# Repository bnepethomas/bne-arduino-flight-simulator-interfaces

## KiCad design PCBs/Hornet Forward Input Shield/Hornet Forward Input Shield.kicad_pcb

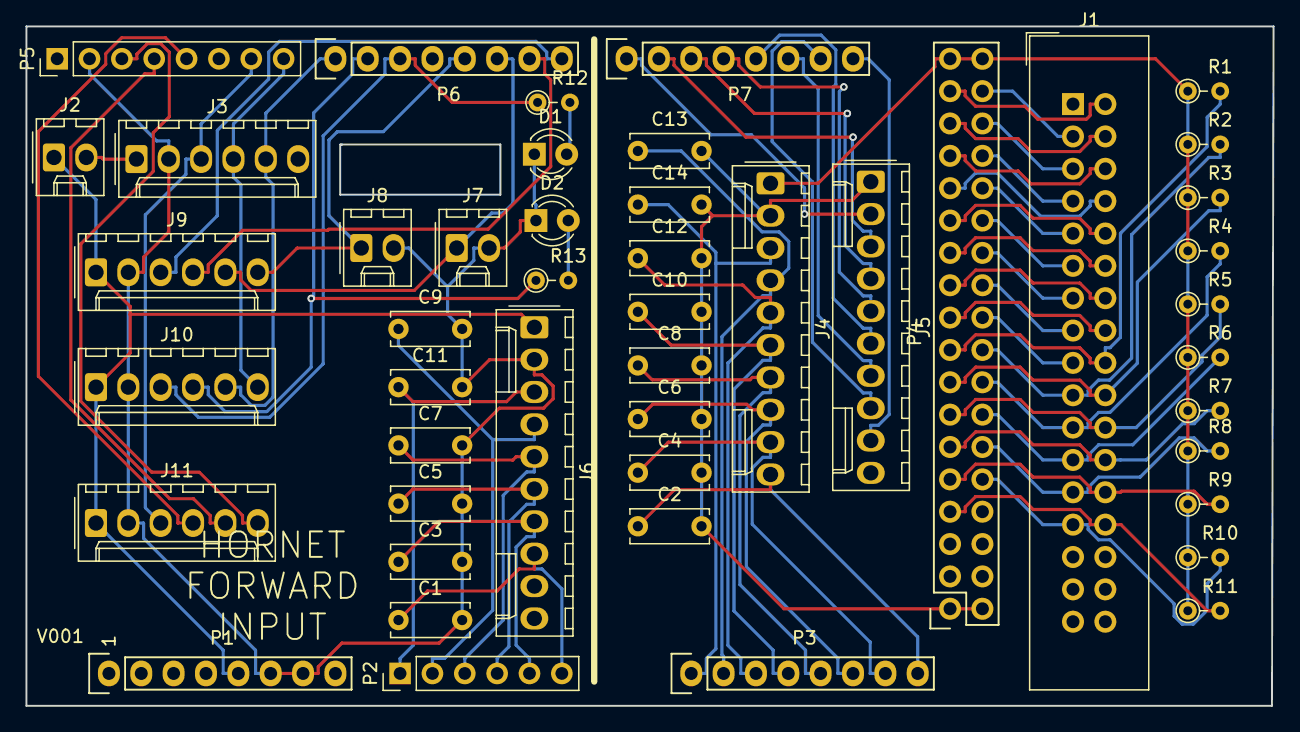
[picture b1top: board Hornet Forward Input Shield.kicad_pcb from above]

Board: 2 copper layers, 97.9 x 53.3 mm, 47 parts (0 on the bottom side), 68 nets.

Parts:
C1, C2, C3, C4, C5, C6, C7, C8, C9, C10, C11, C12, C13, C14: C; C_Disc_D6.0mm_W2.5mm_P5.00mm
D1: GREEN; LED_D3.0mm
D2: RED; LED_D3.0mm
J1: MATRIX INPUT; IDC-Header_2x17_P2.54mm_Vertical
J2: 5V to Max7219; Molex_1x02_P2.54mm_Vertical
J3: 7219 OUT; Molex_1x06_P2.54mm_Vertical
J4: ANALOG B; Molex_1x10_P2.54mm_Vertical
J5: ENCODERS; Molex_1x10_P2.54mm_Vertical
J6: ANALOG A; Molex_1x10_P2.54mm_Vertical
J7: Address Select 0; Molex_1x02_P2.54mm_Vertical
J8: Address Select 1; Molex_1x02_P2.54mm_Vertical
J9: DIGITAL A; Molex_1x06_P2.54mm_Vertical
J10: DIGITAL B; Molex_1x06_P2.54mm_Vertical
J11: DIGITAL C; Molex_1x06_P2.54mm_Vertical
P1: Power; Socket_Strip_Arduino_1x08
P2: Analog; PinHeader_1x06_P2.54mm_Vertical
P3: Analog; Socket_Strip_Arduino_1x08
P4: Digital; Socket_Strip_Arduino_2x18
P5: PWM; PinHeader_1x08_P2.54mm_Vertical
P6: PWM; Socket_Strip_Arduino_1x08
P7: Communication; Socket_Strip_Arduino_1x08
R1, R2, R3, R4, R5, R6, R7, R8, R9, R10, R11, R12, R13: R; PT_R_Axial_DIN0204_L3.6mm_D1.6mm_P2.54mm_Vertical

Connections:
+5V: J4.1, P4.35, P4.36, R1.1, R2.1, R3.1, R4.1, R5.1, R6.1, R7.1, R8.1, R9.1, R10.1, R11.1
+5VL: J2.1, J6.1, J9.1, J10.1, J11.1, P1.5
/14(Tx3): J5.2, P7.1
/15(Rx3): J5.3, P7.2
/16(Tx2): J5.4, P7.3
/17(Rx2): J5.5, P7.4
/18(Tx1): J5.6, P7.5
/19(Rx1): J5.7, P7.6
/20(SDA): J5.8, P7.7
/21(SCL): J5.9, P7.8
/22: J1.2, P4.33
/23: J1.3, P4.34
/24: J1.4, P4.31
/25: J1.5, P4.32
/26: J1.6, P4.29
/27: J1.7, P4.30
/28: J1.8, P4.27
/29: J1.9, P4.28
/30: J1.10, P4.25
/31: J1.11, P4.26
/32: J1.12, P4.23
/33: J1.13, P4.24
/34: J1.14, P4.21
/35: J1.15, P4.22
/36: J1.16, P4.19
/37: J1.17, P4.20
/38: J1.18, P4.17, R1.2
/39: J1.19, P4.18, R2.2
/40: J1.20, P4.15, R3.2
/41: J1.21, P4.16, R4.2
/42: J1.22, P4.13, R5.2
/43: J1.23, P4.14, R6.2
/44: J1.24, P4.11, R7.2
/45: J1.25, P4.12, R8.2
/46: J1.26, P4.9, R9.2
/47: J1.27, P4.10, R10.2
/48: J1.28, P4.7, R11.2
/A0: C11.1, J6.3, P2.1
/A1: C9.1, J6.4, P2.2
/A2: C7.1, J6.5, P2.3
/A3: C5.1, J6.6, P2.4
/A4: C3.1, J6.7, P2.5
/A5: C1.1, J6.8, P2.6
/A8: C14.1, J4.3, P3.1
/A9: C13.1, J4.4, P3.2
/A10: C12.1, J4.5, P3.3
/A11: C10.1, J4.6, P3.4
/A12: C8.1, J4.7, P3.5
/A13: C6.1, J4.8, P3.6
/A14: C4.1, J4.9, P3.7
/A15: C2.1, J4.10, P3.8
/D0: J9.3, P6.8
/D1: J9.4, P6.7
/D2: J7.1, J9.5, P6.6
/D3: J8.1, J9.6, P6.5
/D5: J10.3, P6.3, R12.1
/D6: J10.4, P6.2, R13.1
/D7: J3.5, J10.5, P6.1
/D8: J3.4, J10.6, P5.8
/D9: J3.3, J11.3, P5.7
/D11: J11.4, P5.5
/D12: J11.5, P5.4
/D13: J11.6, P5.3
GND: C2.2, C4.2, C6.2, C8.2, C10.2, C12.2, C13.2, C14.2, J4.2, J5.1, P4.1, P4.2
GNDD: C1.2, C3.2, C5.2, C7.2, C9.2, C11.2, D1.1, D2.1, J3.2, J6.2, J7.2, J8.2, J9.2, J10.2, J11.2, P1.6, P1.7, P5.2
unnamed: D1.2, R12.2
unnamed: D2.2, R13.2
unnamed: J2.2, J3.1

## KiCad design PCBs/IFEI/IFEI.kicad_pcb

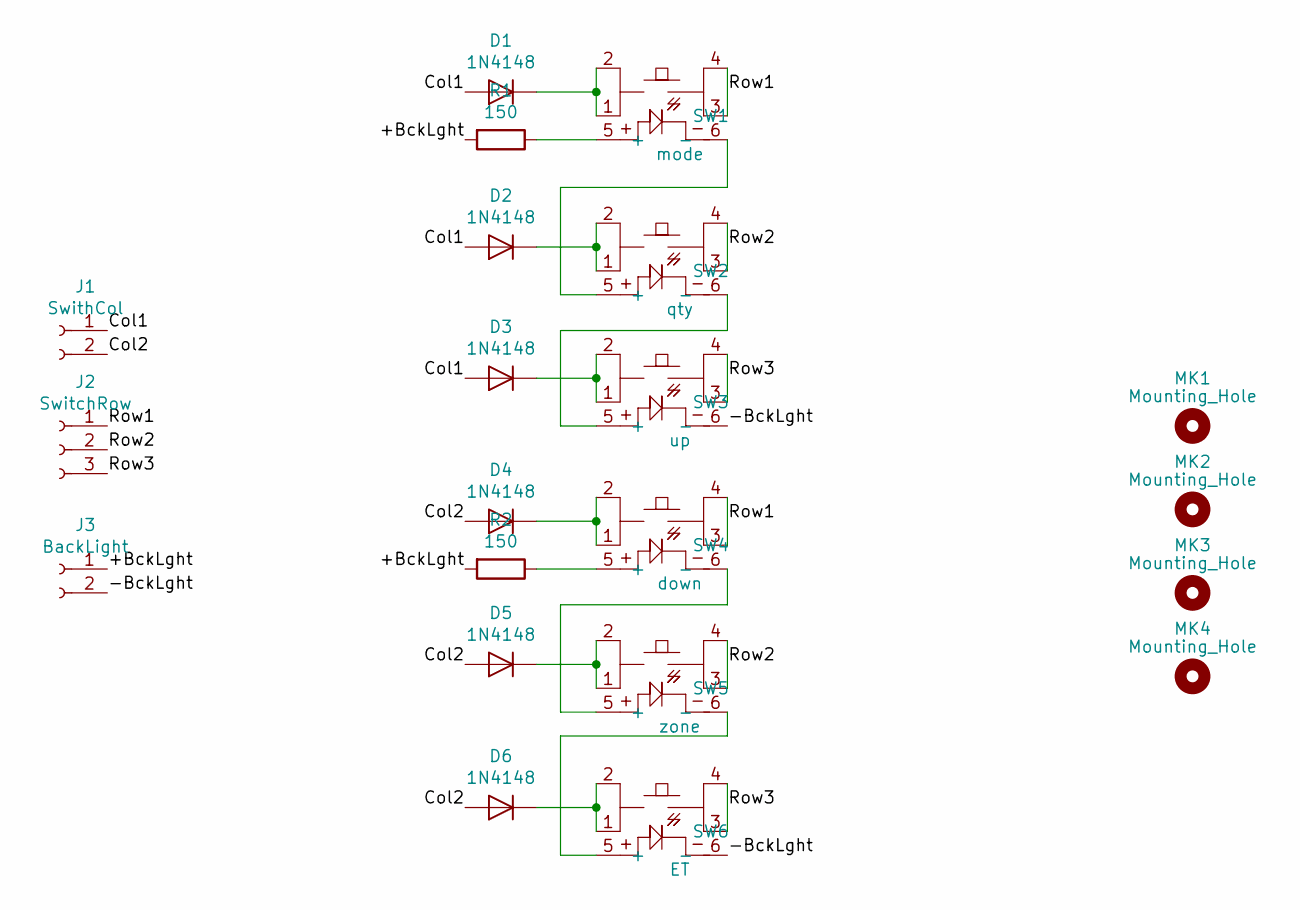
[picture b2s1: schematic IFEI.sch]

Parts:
D1, D2, D3, D4, D5, D6: 1N4148; D_DO-35_SOD27_P7.62mm_Horizontal
J1: SwithCol; Molex_1x02_P2.54mm_Vertical
J2: SwitchRow; Molex_1x03_P2.54mm_Vertical
J3: BackLight; Molex_1x02_P2.54mm_Vertical
MK1, MK2, MK3, MK4: Mounting_Hole; MountingHole_2.2mm_M2
R1, R2: 150; R_Axial_DIN0207_L6.3mm_D2.5mm_P7.62mm_Horizontal
SW1: mode; PT_Small_Tactile_Switch_With_LED
SW2: qty; PT_Small_Tactile_Switch_With_LED
SW3: up; PT_Small_Tactile_Switch_With_LED
SW4: down; PT_Small_Tactile_Switch_With_LED
SW5: zone; PT_Small_Tactile_Switch_With_LED
SW6: ET; PT_Small_Tactile_Switch_With_LED

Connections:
/+BckLght: J3.1, R1.2, R2.2
/-BckLght: J3.2, SW3.6 (-), SW6.6 (-)
/Col1: D1.2 (A), D2.2 (A), D3.2 (A), J1.1
/Col2: D4.2 (A), D5.2 (A), D6.2 (A), J1.2
/Row1: J2.1, SW1.3, SW1.4, SW4.3, SW4.4
/Row2: J2.2, SW2.3, SW2.4, SW5.3, SW5.4
/Row3: J2.3, SW3.3, SW3.4, SW6.3, SW6.4
unnamed: D1.1 (K), SW1.1, SW1.2
unnamed: D2.1 (K), SW2.1, SW2.2
unnamed: D3.1 (K), SW3.1, SW3.2
unnamed: D4.1 (K), SW4.1, SW4.2
unnamed: D5.1 (K), SW5.1, SW5.2
unnamed: D6.1 (K), SW6.1, SW6.2
unnamed: R1.1, SW1.5 (+)
unnamed: R2.1, SW4.5 (+)
unnamed: SW1.6 (-), SW2.5 (+)
unnamed: SW2.6 (-), SW3.5 (+)
unnamed: SW4.6 (-), SW5.5 (+)
unnamed: SW5.6 (-), SW6.5 (+)

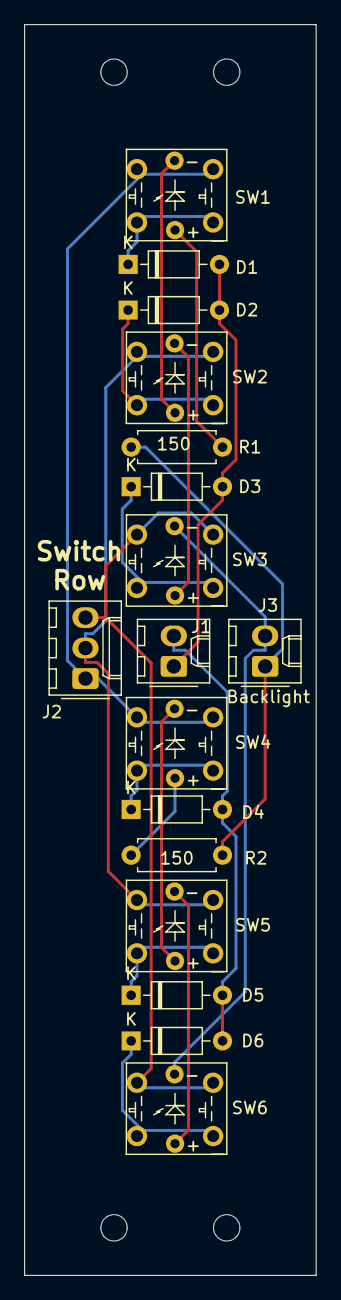
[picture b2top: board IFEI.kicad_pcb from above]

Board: 2 copper layers, 24.3 x 104.3 mm, 21 parts (0 on the bottom side), 19 nets.

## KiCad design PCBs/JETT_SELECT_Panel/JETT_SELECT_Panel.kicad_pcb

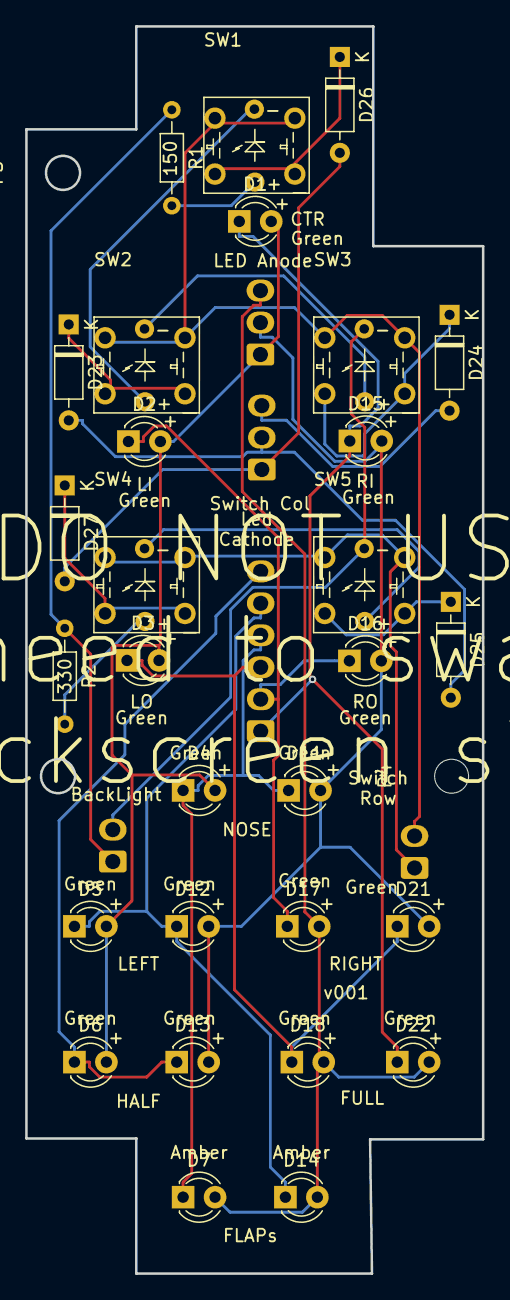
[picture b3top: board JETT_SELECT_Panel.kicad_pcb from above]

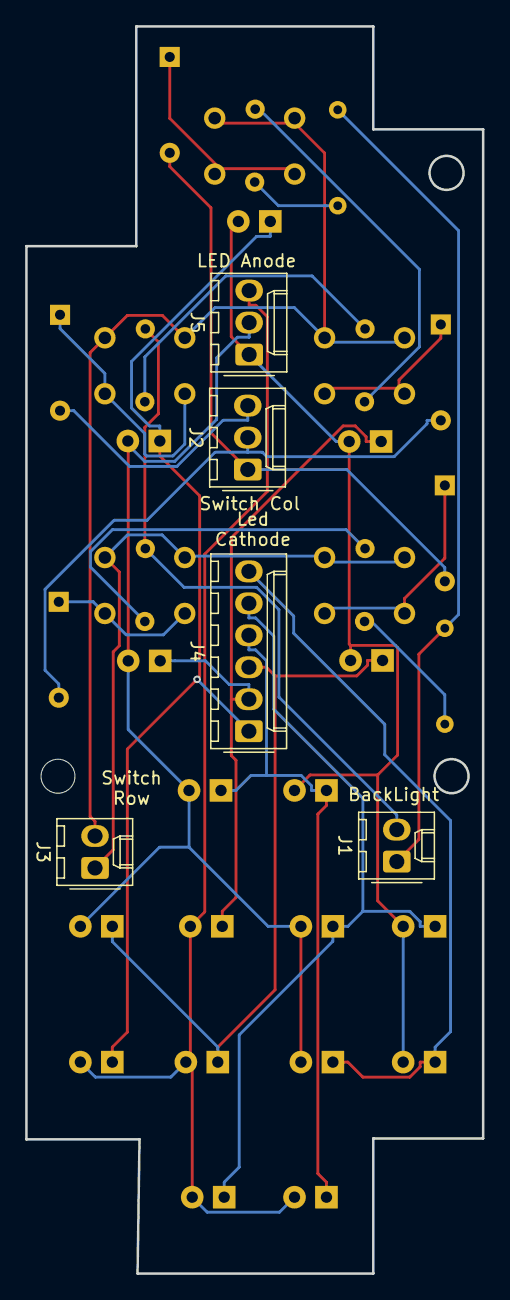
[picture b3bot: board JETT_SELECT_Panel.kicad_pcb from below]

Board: 2 copper layers, 36.3 x 99.1 mm, 36 parts (5 on the bottom side), 26 nets.

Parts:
D1: 0,0; LED_D3.0mm_Clear
D2: 1,0; LED_D3.0mm_Clear
D3: 2,0; LED_D3.0mm_Clear
D4: 3,0; LED_D3.0mm_Clear
D5: 4,0; LED_D3.0mm_Clear
D6: 5,0; LED_D3.0mm_Clear
D7: 6,0; LED_D3.0mm_Clear
D11: 3,1; LED_D3.0mm_Clear
D12: 4,1; LED_D3.0mm_Clear
D13: 5,1; LED_D3.0mm_Clear
D14: 6,1; LED_D3.0mm_Clear
D15: 1,2; LED_D3.0mm_Clear
D16: 2,2; LED_D3.0mm_Clear
D17: 4,2; LED_D3.0mm_Clear
D18: 5,2; LED_D3.0mm_Clear
D21: 4,3; LED_D3.0mm_Clear
D22: 5,3; LED_D3.0mm_Clear
D23, D24, D25, D26, D27: D; D_Signal_P7.62mm_Horizontal
J1: BackLight; Molex_1x02_P2.54mm_Vertical
J2: SwithCol; Molex_1x03_P2.54mm_Vertical
J3: SwitchRow; Molex_1x02_P2.54mm_Vertical
J4: LedCathode; Molex_1x06_P2.54mm_Vertical
J5: LedAnode; Molex_1x03_P2.54mm_Vertical
P3, P4: CONN_01X01; MountingHole_2.7mm_M2.5
R1: 150; R_Axial_DIN0204_L3.6mm_D1.6mm_P7.62mm_Horizontal
R2: 330; R_Axial_DIN0204_L3.6mm_D1.6mm_P7.62mm_Horizontal
SW1, SW2, SW3, SW4, SW5: SW_Push; PT_Small_Tactile_Switch_With_LED

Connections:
/Dig0: D1.1, D15.1, D22.1, J4.1
/Dig1: D2.1, D16.1, D17.1, J4.2
/Dig2: D3.1, D18.1, D21.1, J4.3
/Dig3: D4.1, D7.1, D11.1, J4.4
/Dig4: D5.1, D12.1, D14.1, J4.5
/Dig5: D6.1, D13.1, J4.6
/SegA: D11.2, D12.2, D13.2, D15.2, D16.2, D21.2, J5.2
/SegB: D7.2, D14.2, D17.2, D18.2, D22.2, J5.3
/SegDP: D1.2, D2.2, D3.2, D4.2, D5.2, D6.2, J5.1
unnamed: D23.1, SW2.1, SW2.2
unnamed: D23.2, D25.2, J2.2
unnamed: D24.1, SW3.1, SW3.2
unnamed: D24.2, J2.3
unnamed: D25.1, SW5.1, SW5.2
unnamed: D26.1, SW1.1, SW1.2
unnamed: D26.2, D27.2, J2.1
unnamed: D27.1, SW4.1, SW4.2
unnamed: J1.1, R1.1, R2.1
unnamed: J1.2, SW3.6, SW5.6
unnamed: J3.1, SW4.3, SW4.4, SW5.3, SW5.4
unnamed: J3.2, SW1.3, SW1.4, SW2.3, SW2.4, SW3.3, SW3.4
unnamed: R1.2, SW1.5
unnamed: R2.2, SW4.5
unnamed: SW1.6, SW2.5
unnamed: SW2.6, SW3.5
unnamed: SW4.6, SW5.5

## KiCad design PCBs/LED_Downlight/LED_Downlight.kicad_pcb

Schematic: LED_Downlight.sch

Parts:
D1, D2, D3, D4, D5, D6: LED; LED_D8.0mm
H1, H2, H3, H4, H5: MountingHole; MountingHole_3.2mm_M3
J1, J2: Conn_01x04_Female; PinHeader_1x04_P2.54mm_Horizontal
R1, R2: R_US; R_Axial_DIN0207_L6.3mm_D2.5mm_P7.62mm_Horizontal

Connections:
/+12VGreen: J1.1, J2.1, R1.1
/+12VWhite: J1.3, J2.3, R2.1
/GNDGreen: D3.1 (K), J1.2, J2.2
/GNDWhite: D6.1 (K), J1.4, J2.4
unnamed: D1.1 (K), D2.2 (A)
unnamed: D1.2 (A), R1.2
unnamed: D2.1 (K), D3.2 (A)
unnamed: D4.1 (K), D5.2 (A)
unnamed: D4.2 (A), R2.2
unnamed: D5.1 (K), D6.2 (A)

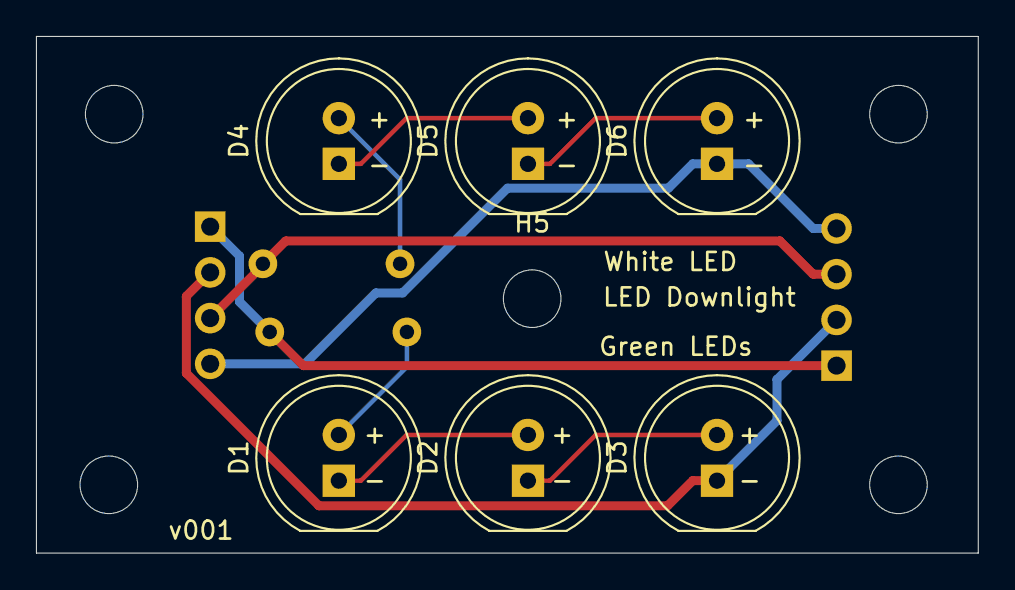
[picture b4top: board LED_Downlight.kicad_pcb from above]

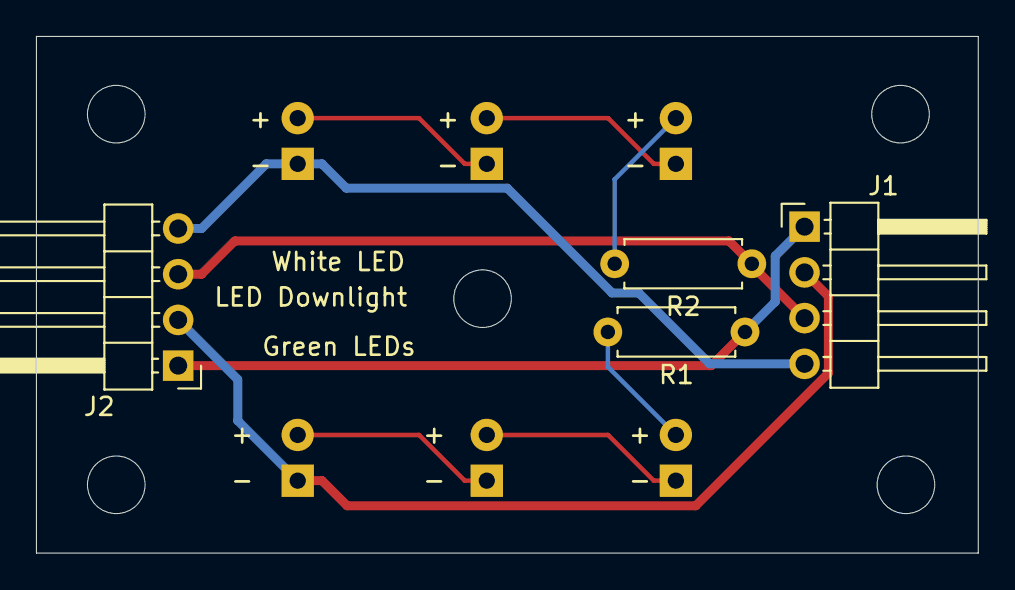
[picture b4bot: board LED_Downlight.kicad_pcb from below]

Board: 2 copper layers, 52.3 x 28.7 mm, 15 parts (4 on the bottom side), 10 nets.

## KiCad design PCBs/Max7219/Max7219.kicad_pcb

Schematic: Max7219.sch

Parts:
C1: C; C_Disc_D5.1mm_W3.2mm_P5.00mm
C2: CP; CP_Radial_D8.0mm_P5.00mm
J1, J2: PinHeader_1x06_P2.54mm_Vertical
J3, J4, J5, J6, J7, J8, J9, J10, J11, J12, J13, J14, J25, J27, J29, J30, J31, J32: PinHeader_1x08_P2.54mm_Vertical
J15: PinHeader_1x10_P2.54mm_Vertical
J16, J17, J18, J19, J20, J21, J22, J23, J24: PinHeader_1x03_P2.54mm_Vertical
J26, J28: TerminalBlock_bornier-2_P5.08mm
R1: R_Axial_DIN0309_L9.0mm_D3.2mm_P5.08mm_Vertical
U1: MAX7219ENG; DIP-24_W7.62mm_Socket
U2: ULN2003A; DIP-16_W7.62mm

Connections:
+5V: C1.1, C2.1, J1.1, J2.1, R1.1, U1.19
+12V: J26.1, J27.8
/5VA: J16.2, J17.2, J18.2, J19.2, J20.2, J21.2, J22.2, J23.2, J24.2, J28.1
/CLK: J1.5, J2.5, U1.13
/Col0: J3.1, J6.1, J8.1, J10.1, J12.1, J14.1, U1.2
/Col1: J3.2, J6.2, J8.2, J10.2, J12.2, J14.2, U1.11
/Col2: J3.3, J6.3, J8.3, J10.3, J12.3, J14.3, U1.6
/Col3: J3.4, J6.4, J8.4, J10.4, J12.4, J14.4, U1.7
/Col4: J3.5, J6.5, J8.5, J10.5, J12.5, J14.5, U1.3
/Col5: J3.6, J6.6, J8.6, J10.6, J12.6, J14.6, U1.10
/Col6: J3.7, J6.7, J8.7, J10.7, J12.7, J14.7, U1.5
/Col7: J3.8, J6.8, J8.8, J10.8, J12.8, J14.8, U1.8
/DIN: J1.3, U1.1
/DOUT: J2.3, U1.24
/In0: J25.1, U2.1 (I1)
/In1: J25.2, U2.2 (I2)
/In2: J25.3, U2.3 (I3)
/In3: J25.4, U2.4 (I4)
/In4: J25.5, U2.5 (I5)
/In5: J25.6, U2.6 (I6)
/In6: J25.7, U2.7 (I7)
/LOAD: J1.4, J2.4, U1.12
/Out0: J27.1, U2.16 (O1)
/Out1: J27.2, U2.15 (O2)
/Out2: J27.3, U2.14 (O3)
/Out3: J27.4, U2.13 (O4)
/Out4: J27.5, U2.12 (O5)
/Out5: J27.6, U2.11 (O6)
/Out6: J27.7, U2.10 (O7)
/Row0: J4.1, J5.1, J7.1, J9.1, J11.1, J13.1, U1.22
/Row1: J4.2, J5.2, J7.2, J9.2, J11.2, J13.2, U1.14
/Row2: J4.3, J5.3, J7.3, J9.3, J11.3, J13.3, U1.16
/Row3: J4.4, J5.4, J7.4, J9.4, J11.4, J13.4, U1.20
/Row4: J4.5, J5.5, J7.5, J9.5, J11.5, J13.5, U1.23
/Row5: J4.6, J5.6, J7.6, J9.6, J11.6, J13.6, U1.21
/Row6: J4.7, J5.7, J7.7, J9.7, J11.7, J13.7, U1.15
/Row7: J4.8, J5.8, J7.8, J9.8, J11.8, J13.8, U1.17
/Servo0: J15.1, J16.3
/Servo1: J15.2, J18.3
/Servo2: J15.3, J20.3
/Servo3: J15.4, J22.3
/Servo4: J15.5, J24.3
/Servo5: J15.6, J17.3
/Servo6: J15.7, J19.3
/Servo7: J15.8, J21.3
/Servo8: J15.9, J23.3
GND: C1.2, C2.2, J1.2, J2.2, U1.4, U1.9
GNDA: J15.10, J16.1, J17.1, J18.1, J19.1, J20.1, J21.1, J22.1, J23.1, J24.1, J28.2
GNDD: J25.8, J26.2, U2.8 (GND)
unnamed: J29.1, J30.1
unnamed: J29.2, J30.2
unnamed: J29.3, J30.3
unnamed: J29.4, J30.4
unnamed: J29.5, J30.5
unnamed: J29.6, J30.6
unnamed: J29.7, J30.7
unnamed: J29.8, J30.8
unnamed: J31.1, J32.1
unnamed: J31.2, J32.2
unnamed: J31.3, J32.3
unnamed: J31.4, J32.4
unnamed: J31.5, J32.5
unnamed: J31.6, J32.6
unnamed: J31.7, J32.7
unnamed: J31.8, J32.8
unnamed: R1.2, U1.18

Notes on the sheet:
Digits = Columns = Cathodes Segments = Rows = Anodes

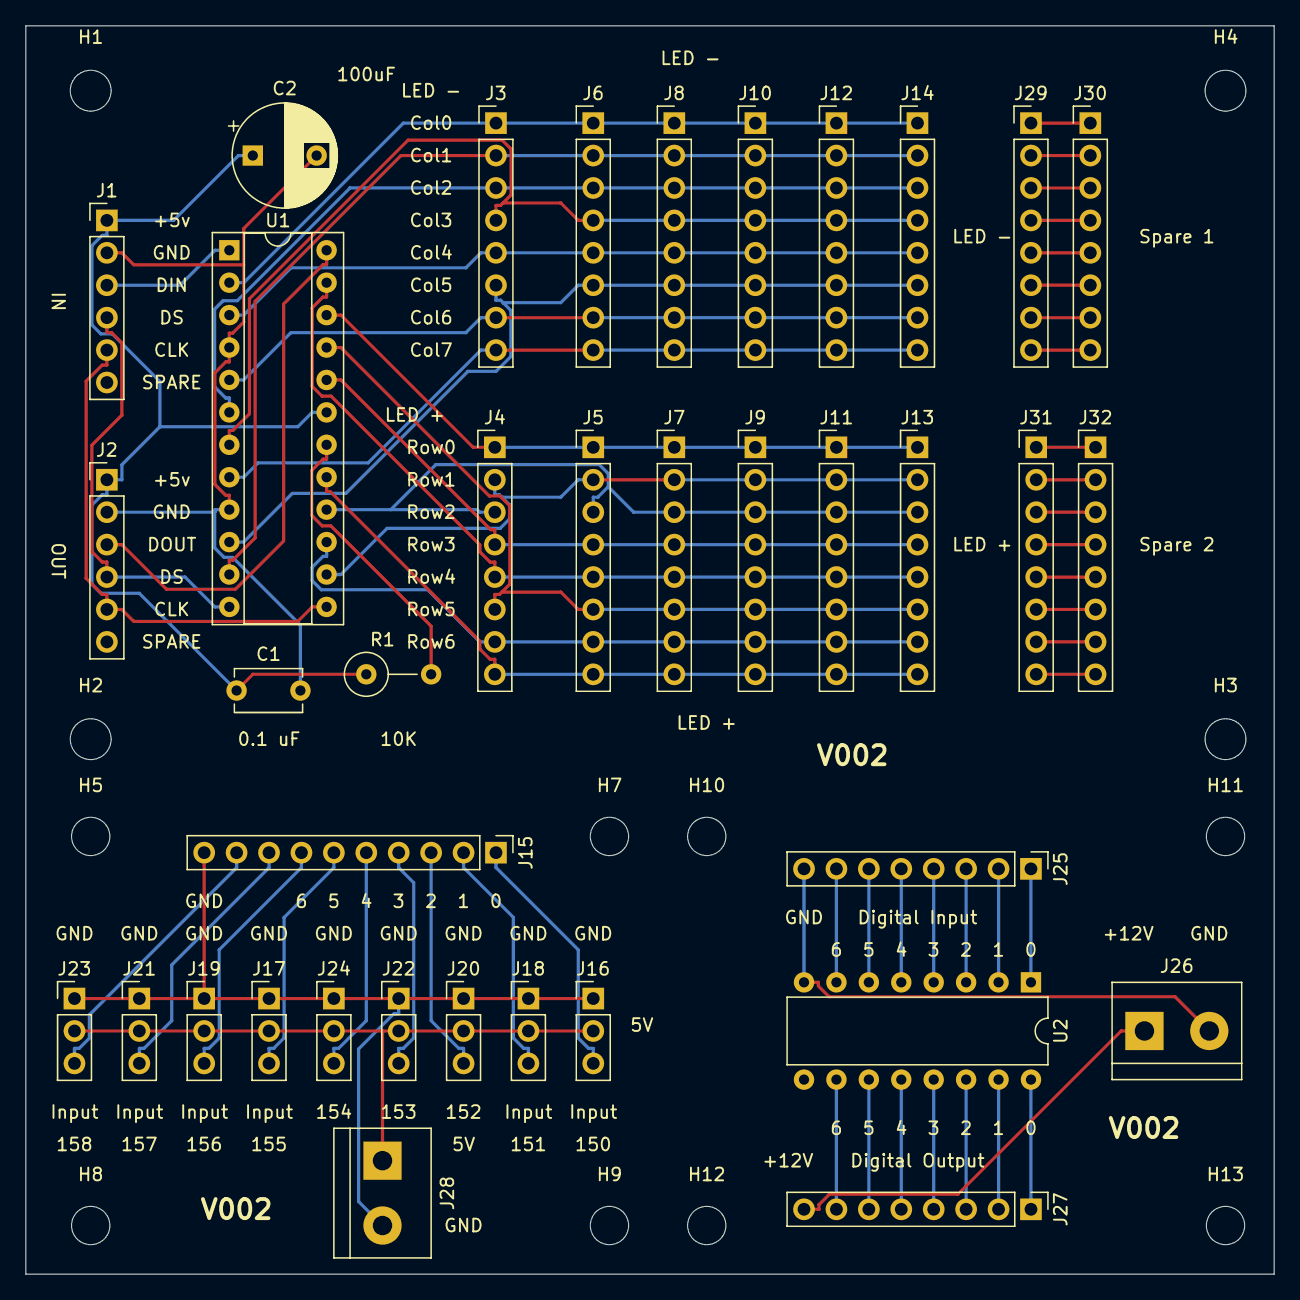
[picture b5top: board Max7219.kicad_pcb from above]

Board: 2 copper layers, 97.8 x 97.8 mm, 49 parts (0 on the bottom side), 66 nets.

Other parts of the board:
H1, H2, H3, H4: MountingHole_3.2mm_M3
H5, H7, H8, H9, H10, H11, H12, H13: MountingHole_3mm

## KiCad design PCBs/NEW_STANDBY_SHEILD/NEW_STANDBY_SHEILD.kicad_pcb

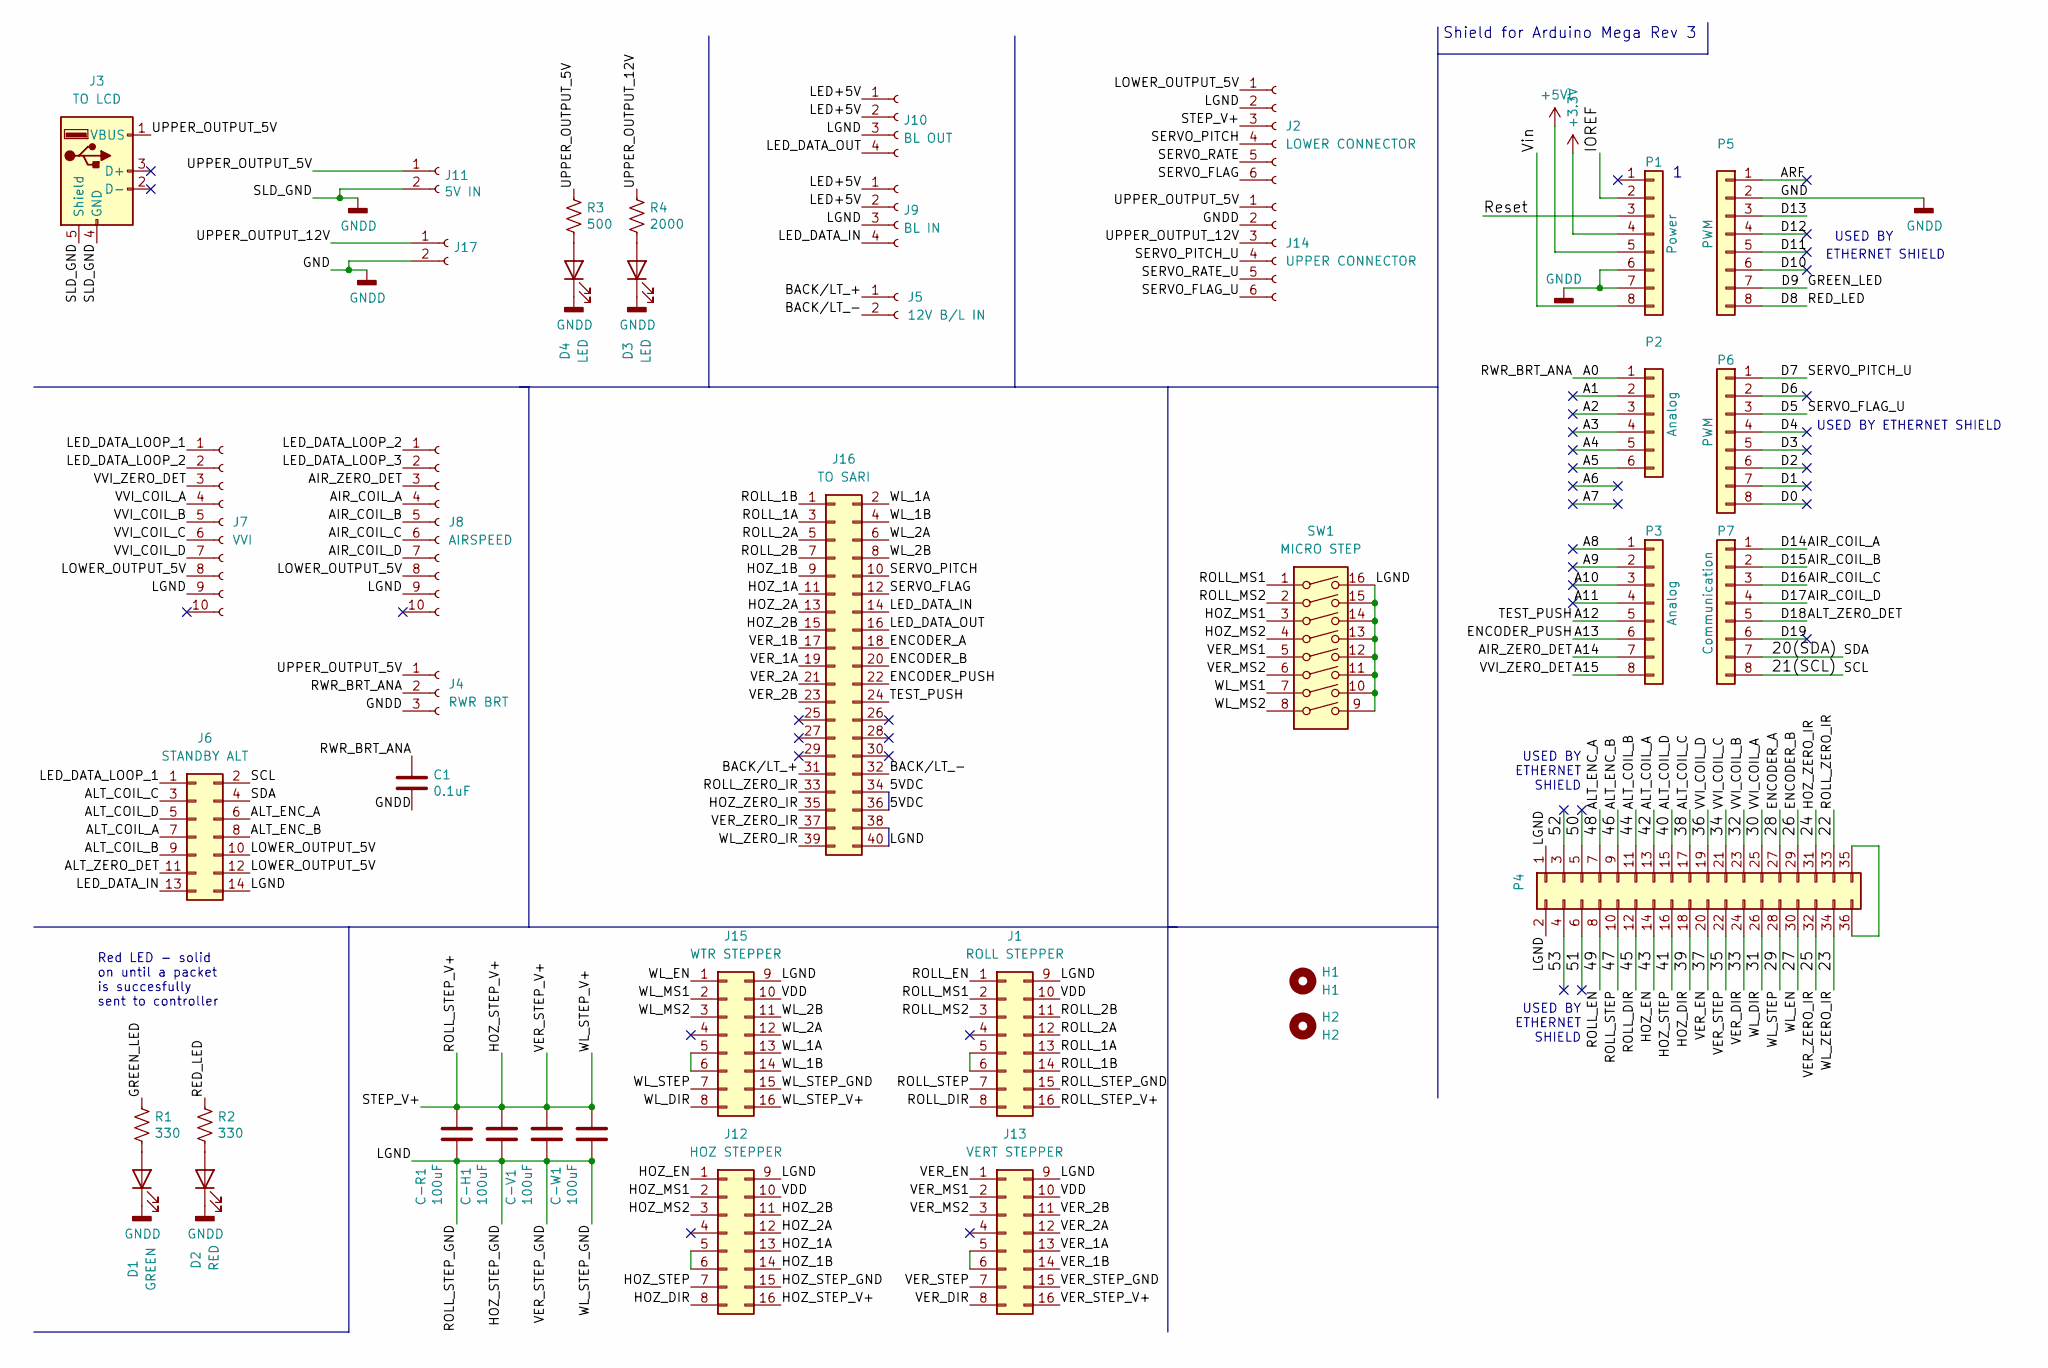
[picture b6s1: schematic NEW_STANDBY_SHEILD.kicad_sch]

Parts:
C1: 0.1uF; C_Disc_D6.0mm_W2.5mm_P5.00mm
C-H1: 100uF; C_Radial_D8.0mm_H7.0mm_P3.50mm
C-R1: 100uF; C_Radial_D8.0mm_H7.0mm_P3.50mm
C-V1: 100uF; C_Radial_D8.0mm_H7.0mm_P3.50mm
C-W1: 100uF; C_Radial_D8.0mm_H7.0mm_P3.50mm
D1: GREEN; LED_D3.0mm
D2: RED; LED_D3.0mm
D3, D4: LED; LED_D3.0mm
H1: H1; MountingHole_2.5mm
H2: H2; MountingHole_2.5mm
J1: ROLL STEPPER; Pololu_Breakout-16_15.2x20.3mm
J2: LOWER CONNECTOR; JST_XH_B6B-XH-A_1x06_P2.50mm_Vertical
J3: TO LCD; USB_A_Molex_67643_Horizontal
J4: RWR BRT; JST_XH_B3B-XH-A_1x03_P2.50mm_Vertical
J5: 12V B/L IN; JST_EH_B2B-EH-A_1x02_P2.50mm_Vertical
J6: STANDBY ALT; IDC-Header_2x07_P2.54mm_Vertical
J7: VVI; JST_XH_B10B-XH-A_1x10_P2.50mm_Vertical
J8: AIRSPEED; JST_XH_B10B-XH-A_1x10_P2.50mm_Vertical
J9: BL IN; Molex_Mini-Fit_Jr_5566-04A_2x02_P4.20mm_Vertical
J10: BL OUT; Molex_Mini-Fit_Jr_5566-04A_2x02_P4.20mm_Vertical
J11: 5V IN; BarrelJack_Horizontal
J12: HOZ STEPPER; Pololu_Breakout-16_15.2x20.3mm
J13: VERT STEPPER; Pololu_Breakout-16_15.2x20.3mm
J14: UPPER CONNECTOR; JST_XH_B6B-XH-A_1x06_P2.50mm_Vertical
J15: WTR STEPPER; Pololu_Breakout-16_15.2x20.3mm
J16: TO SARI; IDC-Header_2x20_P2.54mm_Vertical
J17: STEPPER IN 12-20VDC; BarrelJack_Horizontal
P1: Power; Socket_Strip_Arduino_1x08
P2: Analog; PinHeader_1x06_P2.54mm_Vertical
P3: Analog; Socket_Strip_Arduino_1x08
P4: Digital; Socket_Strip_Arduino_2x18
P5, P6: PWM; Socket_Strip_Arduino_1x08
P7: Communication; Socket_Strip_Arduino_1x08
R1: 330; R_Axial_DIN0204_L3.6mm_D1.6mm_P2.54mm_Vertical
R2: 330; PT_R_Axial_DIN0204_L3.6mm_D1.6mm_P2.54mm_Vertical
R3: 500; R_Axial_DIN0204_L3.6mm_D1.6mm_P2.54mm_Vertical
R4: 2000; R_Axial_DIN0204_L3.6mm_D1.6mm_P2.54mm_Vertical
SW1: MICRO STEP; SW_DIP_SPSTx08_Slide_9.78x22.5mm_W7.62mm_P2.54mm

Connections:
+3V3: P1.4
+5VL: P1.5
/5VDC: J16.34, J16.36
/20(SDA): J6.4, P7.7
/21(SCL): J6.2, P7.8
/22: J16.33, P4.33
/23: J16.39, P4.34
/24: J16.35, P4.31
/25: J16.37, P4.32
/26: J16.20, P4.29
/27: J15.1, P4.30
/28: J16.18, P4.27
/29: J15.7, P4.28
/30: J7.4, P4.25
/31: J15.8, P4.26
/32: J7.5, P4.23
/33: J13.8, P4.24
/34: J7.6, P4.21
/35: J13.7, P4.22
/36: J7.7, P4.19
/37: J13.1, P4.20
/38: J6.3, P4.17
/39: J12.8, P4.18
/40: J6.5, P4.15
/41: J12.7, P4.16
/42: J6.7, P4.13
/43: J12.1, P4.14
/44: J6.9, P4.11
/45: J1.8, P4.12
/46: J6.8, P4.9
/47: J1.7, P4.10
/48: J6.6, P4.7
/49: J1.1, P4.8
/50: P4.5
/51: P4.6
/52: P4.3
/53: P4.4
/A0: C1.1, J4.2, P2.1
/A1: P2.2
/A2: P2.3
/A3: P2.4
/A4: P2.5
/A5: P2.6
/A8: P3.1
/A9: P3.2
/A10: P3.3
/A11: P3.4
/A12: J16.24, P3.5
/A13: J16.22, P3.6
/A14: J8.3, P3.7
/A15: J7.3, P3.8
/AIR_COIL_A: J8.4, P7.1
/AIR_COIL_B: J8.5, P7.2
/AIR_COIL_C: J8.6, P7.3
/AIR_COIL_D: J8.7, P7.4
/ALT_ZERO_DET: J6.11, P7.5
/ARF: P5.1
/BACK/LT_+: J5.1, J16.31
/BACK/LT_-: J5.2, J16.32
/D0: P6.8
/D1: P6.7
/D2: P6.6
/D3: P6.5
/D4: P6.4
/D5: J14.6, P6.3
/D6: P6.2
/D7: J14.4, P6.1
/D8: P5.8, R2.1
/D9: P5.7, R1.1
/D10: P5.6
/D11: P5.5
/D12: P5.4
/D13: P5.3
/D19: P7.6
/HOZ_1A: J12.13, J16.11
/HOZ_1B: J12.14, J16.9
/HOZ_2A: J12.12, J16.13
/HOZ_2B: J12.11, J16.15
/HOZ_MS1: J12.2, SW1.3
/HOZ_MS2: J12.3, SW1.4
/HOZ_STEP_GND: C-H1.2, C-R1.2, C-V1.2, C-W1.2, J1.9, J1.15, J2.2, J6.14, J7.9, J8.9, J9.3, J10.3, J12.9, J12.15, J13.9, J13.15, J15.9, J15.15, J16.38, J16.40, P4.1, P4.2, SW1.9, SW1.10, SW1.11, SW1.12, SW1.13, SW1.14, SW1.15, SW1.16
/HOZ_STEP_V+: C-H1.1, C-R1.1, C-V1.1, C-W1.1, J1.16, J2.3, J12.16, J13.16, J15.16
/IOREF: P1.2
/LED+5V: J9.1, J9.2, J10.1, J10.2
/LED_DATA_IN: J6.13, J9.4, J16.14
/LED_DATA_LOOP_1: J6.1, J7.1
/LED_DATA_LOOP_2: J7.2, J8.1
/LED_DATA_LOOP_3: J8.2
/LED_DATA_OUT: J10.4, J16.16
/LOWER_OUTPUT_5V: J2.1, J6.10, J6.12, J7.8, J8.8
/ROLL_1A: J1.13, J16.3
/ROLL_1B: J1.14, J16.1
/ROLL_2A: J1.12, J16.5
/ROLL_2B: J1.11, J16.7
/ROLL_MS1: J1.2, SW1.1
/ROLL_MS2: J1.3, SW1.2
/Reset: P1.3
/SERVO_FLAG: J2.6, J16.12
/SERVO_PITCH: J2.4, J16.10
/SERVO_RATE: J2.5
/SERVO_RATE_U: J14.5
/UPPER_OUTPUT_5V: J3.1 (VBUS), J4.1, J11.1, J14.1, R3.1
/UPPER_OUTPUT_12V: J14.3, J17.1, R4.1
/VDD: J1.10, J12.10, J13.10, J15.10
/VER_1A: J13.13, J16.19
/VER_1B: J13.14, J16.17
/VER_2A: J13.12, J16.21
/VER_2B: J13.11, J16.23
/VER_MS1: J13.2, SW1.5
/VER_MS2: J13.3, SW1.6
/Vin: P1.8
/WL_1A: J15.13, J16.2
/WL_1B: J15.14, J16.4
/WL_2A: J15.12, J16.6
/WL_2B: J15.11, J16.8
/WL_MS1: J15.2, SW1.7
/WL_MS2: J15.3, SW1.8
GNDD: C1.2, D1.1 (K), D2.1 (K), D3.1 (K), D4.1 (K), J3.4 (GND), J3.5 (Shield), J4.3, J11.2, J14.2, J17.2, P1.6, P1.7, P5.2
unnamed: D1.2 (A), R1.2
unnamed: D3.2 (A), R4.2
unnamed: D4.2 (A), R3.2
unnamed: J1.5, J1.6
unnamed: J12.5, J12.6
unnamed: J13.5, J13.6
unnamed: J15.5, J15.6
unnamed: P4.35, P4.36

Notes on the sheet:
Shield for Arduino Mega Rev 3
USED BY ETHERNET SHIELD
ETHERNET SHIELD
USED BY ETHERNET SHIELD
Red LED - solid on until a packet is succesfully sent to controller
USED BY

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
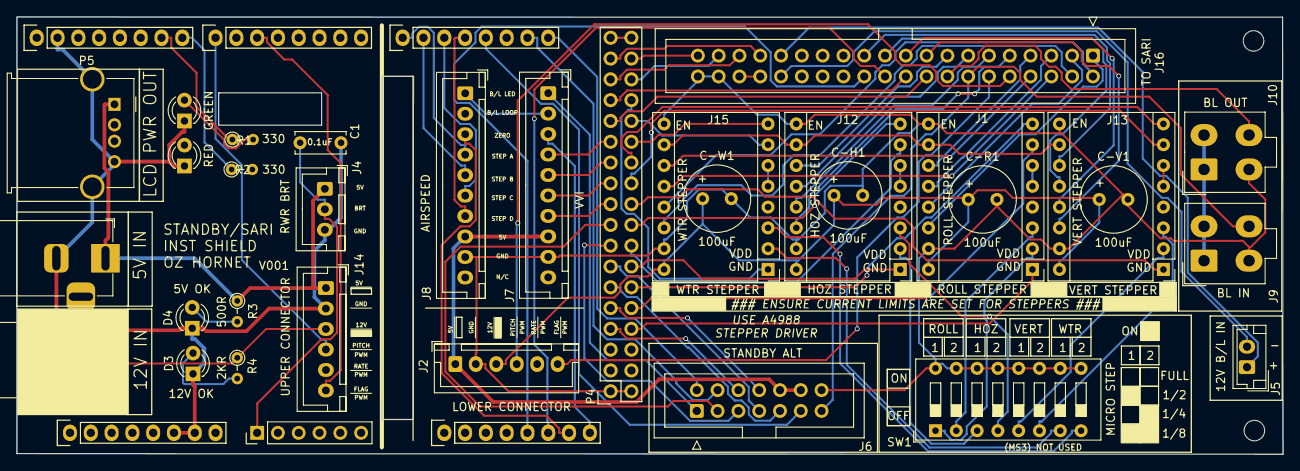
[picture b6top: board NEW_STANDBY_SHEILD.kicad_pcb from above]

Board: 2 copper layers, 154.7 x 53.4 mm, 40 parts (0 on the bottom side), 93 nets.
